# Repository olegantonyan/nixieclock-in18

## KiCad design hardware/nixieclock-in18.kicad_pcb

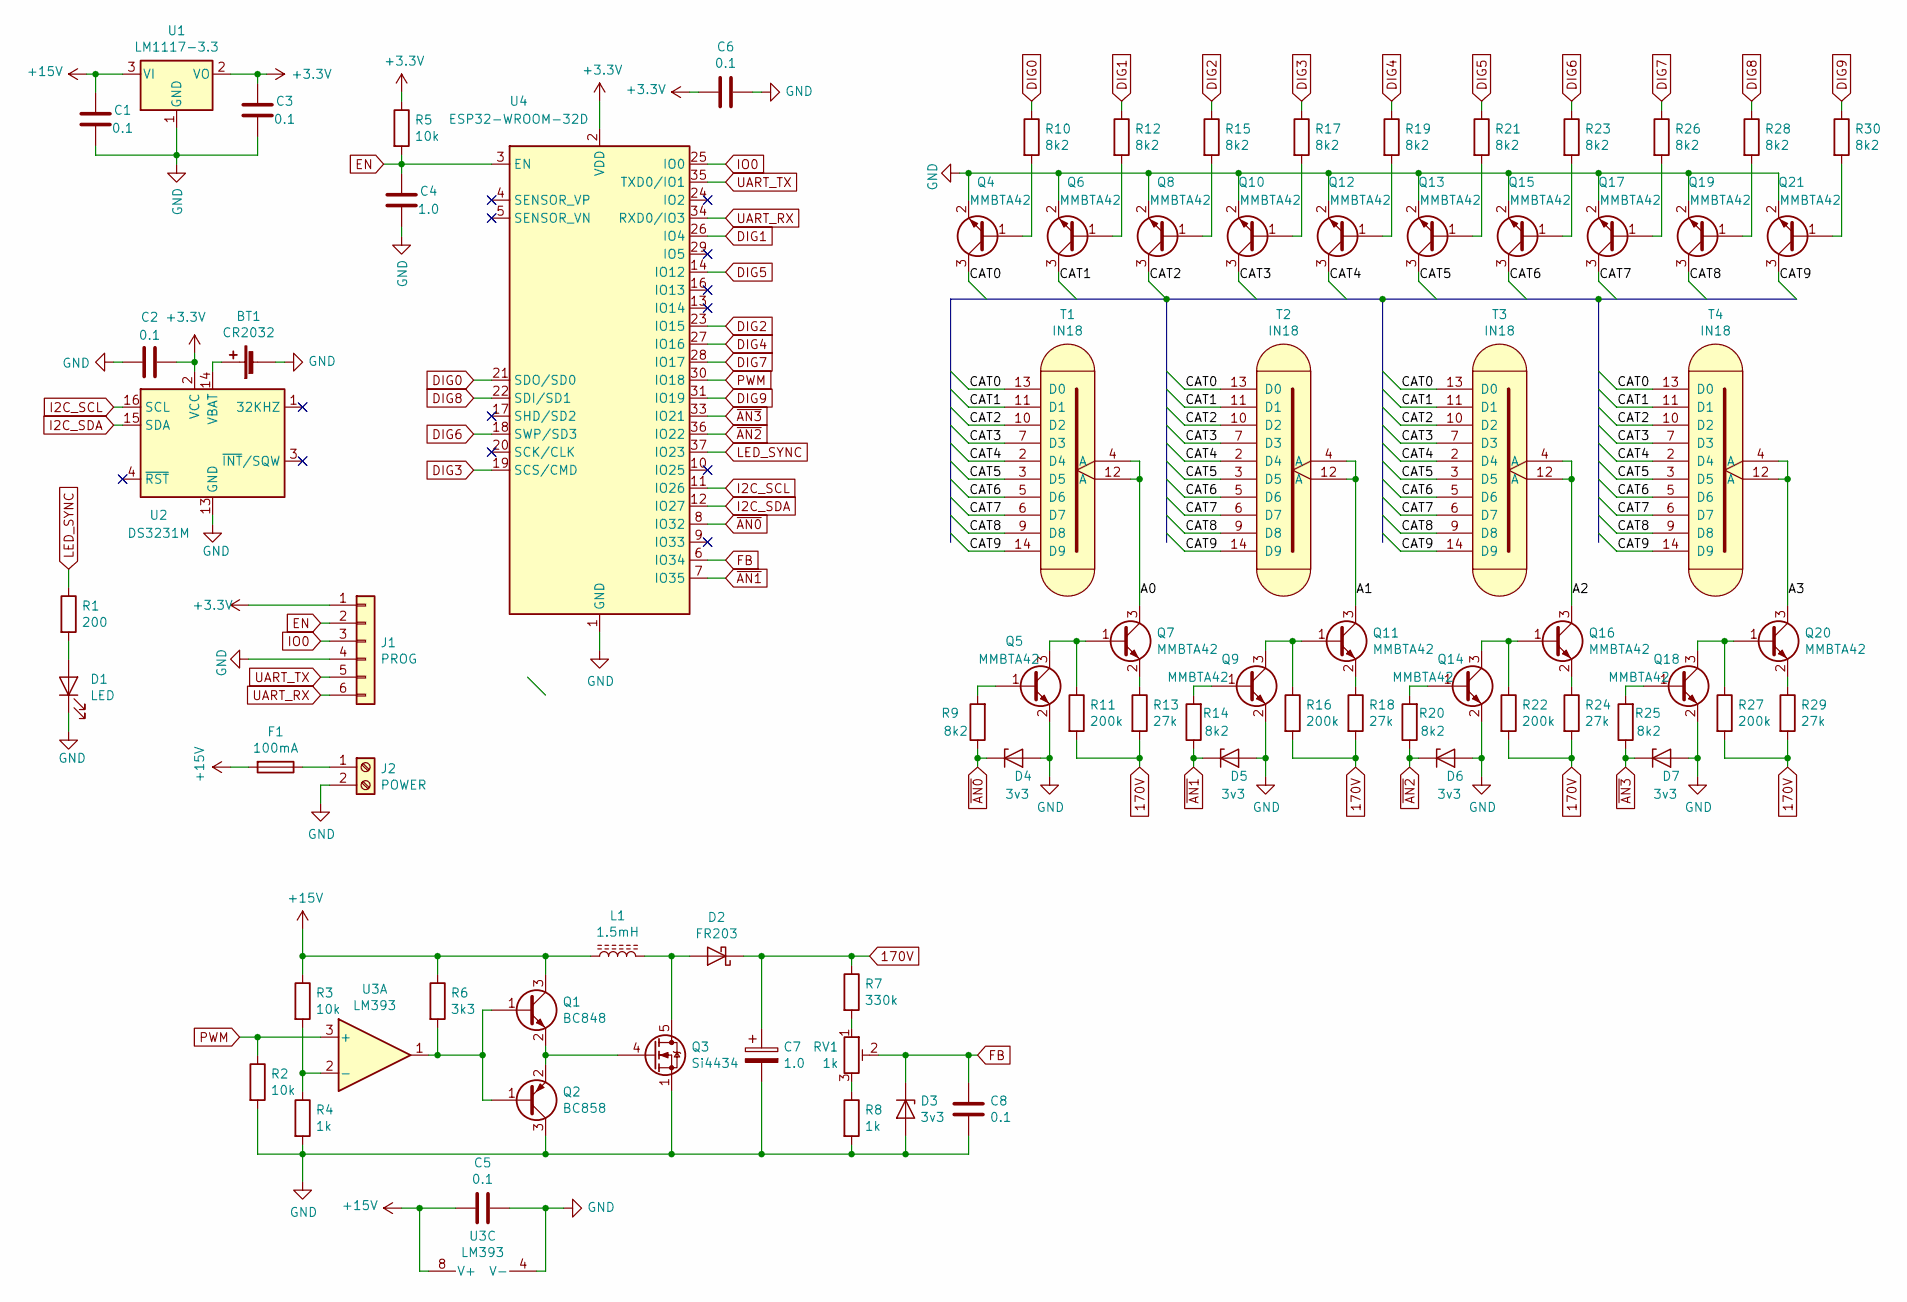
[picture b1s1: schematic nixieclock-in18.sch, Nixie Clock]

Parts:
BT1: CR2032; Keystone_103_1x20mm-CoinCell
C1, C2, C3, C5, C6, C8: 0.1; C_0805_HandSoldering
C4: 1.0; C_0805_HandSoldering
C7: 1.0; CP_Radial_D10.0mm_P5.00mm
D1: LED; LED_D3.0mm_FlatTop
D2: FR203; D_A-405_P10.16mm_Horizontal
D3, D4, D5, D6, D7: 3v3; D_DO-41_SOD81_P7.62mm_Horizontal
F1: 100mA; R_0805_HandSoldering
J1: PROG; Pin_Header_Straight_1x06_Pitch2.54mm
J2: POWER; TerminalBlock_bornier-2_P5.08mm
L1: 1.5mH; L_Radial_D12.0mm_P6.00mm_MuRATA_1900R
Q1: BC848; SOT-23_Handsoldering
Q2: BC858; SOT-23_Handsoldering
Q3: Si4434; PowerPAK_SO-8_Single
Q4, Q5, Q6, Q7, Q8, Q9, Q10, Q11, Q12, Q13, Q14, Q15, Q16, Q17, Q18, Q19, Q20, Q21: MMBTA42; SOT-23_Handsoldering
R1: 200; R_0805_HandSoldering
R2, R3, R5: 10k; R_0805_HandSoldering
R4: 1k; R_0805_HandSoldering
R6: 3k3; R_0805_HandSoldering
R7: 330k; R_Axial_DIN0207_L6.3mm_D2.5mm_P10.16mm_Horizontal
R8: 1k; R_Axial_DIN0207_L6.3mm_D2.5mm_P10.16mm_Horizontal
R9, R10, R12, R14, R15, R17, R19, R20, R21, R23, R25, R26, R28, R30: 8k2; R_0805_HandSoldering
R11, R16, R22, R27: 200k; R_0805_HandSoldering
R13, R18, R24, R29: 27k; R_0805_HandSoldering
RV1: 1k; Potentiometer_Trimmer_ACP_CA6v_Horizontal
T1, T2, T3, T4: IN18
U1: LM1117-3.3; SOT-223
U2: DS3231M; SOIC-16W_7.5x10.3mm_Pitch1.27mm
U3: LM393; SOIC-8_3.9x4.9mm_Pitch1.27mm
U4: ESP32-WROOM-32D; ESP32-WROOM

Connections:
170V: C7.1, D2.1 (K), R7.1, R11.2, R13.2, R16.2, R18.2, R22.2, R24.2, R27.2, R29.2
+3V3: C2.2, C3.2, C6.2, J1.1, R5.1, U1.2 (VO), U2.2 (VCC), U4.2 (VDD)
+15V: C1.2, C5.2, F1.2, L1.1, Q1.3 (C), R3.1, R6.1, U1.3 (VI), U3.8 (V+)
/A0: Q7.3 (C), T1.4 (A), T1.12 (A)
/A1: Q11.3 (C), T2.4 (A), T2.12 (A)
/A2: Q16.3 (C), T3.4 (A), T3.12 (A)
/A3: Q20.3 (C), T4.4 (A), T4.12 (A)
/CAT0: Q4.3 (C), T1.13 (D0), T2.13 (D0), T3.13 (D0), T4.13 (D0)
/CAT1: Q6.3 (C), T1.11 (D1), T2.11 (D1), T3.11 (D1), T4.11 (D1)
/CAT2: Q8.3 (C), T1.10 (D2), T2.10 (D2), T3.10 (D2), T4.10 (D2)
/CAT3: Q10.3 (C), T1.7 (D3), T2.7 (D3), T3.7 (D3), T4.7 (D3)
/CAT4: Q12.3 (C), T1.2 (D4), T2.2 (D4), T3.2 (D4), T4.2 (D4)
/CAT5: Q13.3 (C), T1.3 (D5), T2.3 (D5), T3.3 (D5), T4.3 (D5)
/CAT6: Q15.3 (C), T1.5 (D6), T2.5 (D6), T3.5 (D6), T4.5 (D6)
/CAT7: Q17.3 (C), T1.6 (D7), T2.6 (D7), T3.6 (D7), T4.6 (D7)
/CAT8: Q19.3 (C), T1.9 (D8), T2.9 (D8), T3.9 (D8), T4.9 (D8)
/CAT9: Q21.3 (C), T1.14 (D9), T2.14 (D9), T3.14 (D9), T4.14 (D9)
DIG0: R10.1, U4.21 (SDO/SD0)
DIG1: R12.1, U4.26 (IO4)
DIG2: R15.1, U4.23 (IO15)
DIG3: R17.1, U4.19 (SCS/CMD)
DIG4: R19.1, U4.27 (IO16)
DIG5: R21.1, U4.14 (IO12)
DIG6: R23.1, U4.18 (SWP/SD3)
DIG7: R26.1, U4.28 (IO17)
DIG8: R28.1, U4.22 (SDI/SD1)
DIG9: R30.1, U4.31 (IO19)
EN: C4.2, J1.2, R5.2, U4.3 (EN)
FB: C8.1, D3.1 (K), RV1.2, U4.6 (IO34)
GND: BT1.2 (-), C1.1, C2.1, C3.1, C4.1, C5.1, C6.1, C7.2, C8.2, D1.1 (K), D3.2 (A), D4.2 (A), D5.2 (A), D6.2 (A), D7.2 (A), J1.4, J2.2, Q2.3 (C), Q3.1 (S), Q3.2 (S), Q3.3 (S), Q4.2 (E), Q5.2 (E), Q6.2 (E), Q8.2 (E), Q9.2 (E), Q10.2 (E), Q12.2 (E), Q13.2 (E), Q14.2 (E), Q15.2 (E), Q17.2 (E), Q18.2 (E), Q19.2 (E), Q21.2 (E), R2.2, R4.2, R8.2, U1.1 (GND), U2.5 (GND), U2.6 (GND), U2.7 (GND), U2.8 (GND), U2.9 (GND), U2.10 (GND), U2.11 (GND), U2.12 (GND), U2.13 (GND), U3.4 (V-), U4.1 (GND), U4.15 (GND), U4.38 (GND)
I2C_SCL: U2.16 (SCL), U4.11 (IO26)
I2C_SDA: U2.15 (SDA), U4.12 (IO27)
IO0: J1.3, U4.25 (IO0)
LED_SYNC: R1.1, U4.37 (IO23)
unnamed: BT1.1 (+), U2.14 (VBAT)
unnamed: D1.2 (A), R1.2
unnamed: D2.2 (A), L1.2, Q3.5 (D)
unnamed: F1.1, J2.1
unnamed: Q1.1 (B), Q2.1 (B), R6.2, U3.1
unnamed: Q1.2 (E), Q2.2 (E), Q3.4 (G)
unnamed: Q4.1 (B), R10.2
unnamed: Q5.1 (B), R9.2
unnamed: Q5.3 (C), Q7.1 (B), R11.1
unnamed: Q6.1 (B), R12.2
unnamed: Q7.2 (E), R13.1
unnamed: Q8.1 (B), R15.2
unnamed: Q9.1 (B), R14.2
unnamed: Q10.1 (B), R17.2
unnamed: Q9.3 (C), Q11.1 (B), R16.1
unnamed: Q11.2 (E), R18.1
unnamed: Q12.1 (B), R19.2
unnamed: Q13.1 (B), R21.2
unnamed: Q14.1 (B), R20.2
unnamed: Q14.3 (C), Q16.1 (B), R22.1
unnamed: Q15.1 (B), R23.2
unnamed: Q16.2 (E), R24.1
unnamed: Q17.1 (B), R26.2
unnamed: Q18.1 (B), R25.2
unnamed: Q18.3 (C), Q20.1 (B), R27.1
unnamed: Q19.1 (B), R28.2
unnamed: Q20.2 (E), R29.1
unnamed: Q21.1 (B), R30.2
unnamed: R3.2, R4.1, U3.2 (-)
unnamed: R7.2, RV1.1
unnamed: R8.1, RV1.3
PWM: R2.1, U3.3 (+), U4.30 (IO18)
UART_RX: J1.6, U4.34 (RXD0/IO3)
UART_TX: J1.5, U4.35 (TXD0/IO1)
~AN0: D4.1 (K), R9.1, U4.8 (IO32)
~AN1: D5.1 (K), R14.1, U4.7 (IO35)
~AN2: D6.1 (K), R20.1, U4.36 (IO22)
~AN3: D7.1 (K), R25.1, U4.33 (IO21)

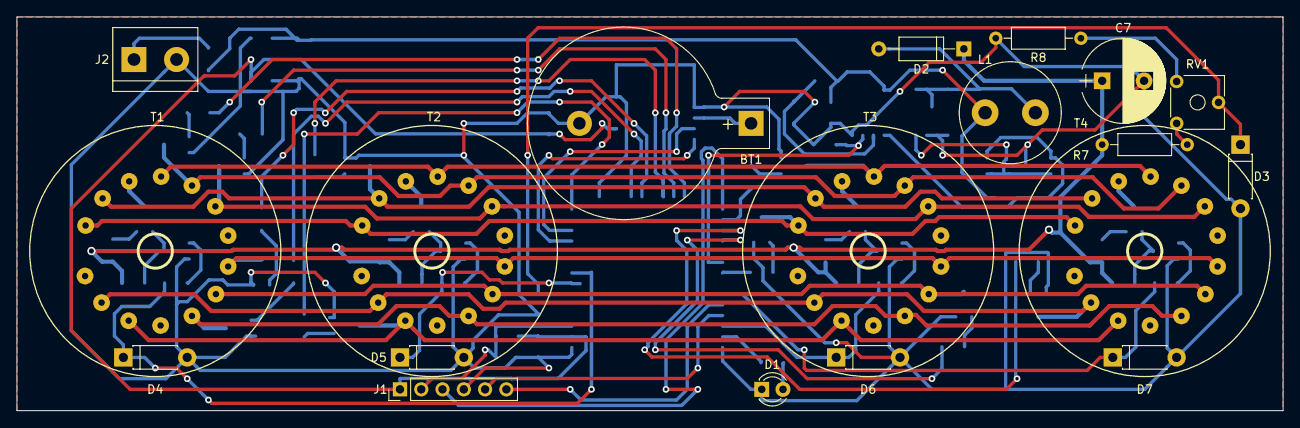
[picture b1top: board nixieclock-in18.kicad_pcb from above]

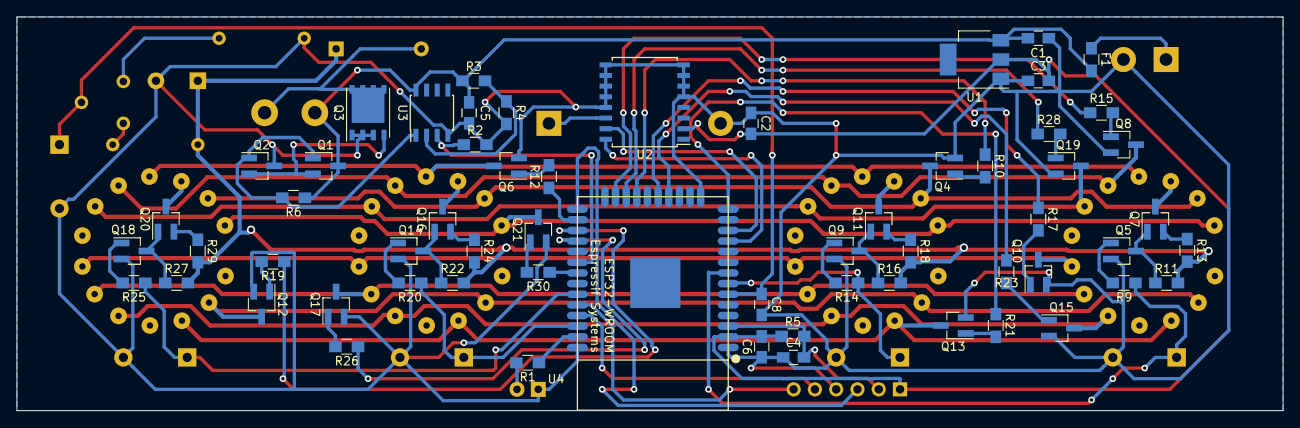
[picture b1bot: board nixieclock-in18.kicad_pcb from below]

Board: 2 copper layers, 151.1 x 47.0 mm, 80 parts (61 on the bottom side), 72 nets.

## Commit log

2019-08-26 initial
2019-08-26 initial 2
2019-08-26 working pwm
2019-08-29 pwm+adc works
2019-08-29 moar schematic
2019-08-31 pcb begins
2019-09-01 fix mmbta42 pinout
2019-09-03 finished pcb
2019-09-03 add fuse
2019-09-03 gerbers
2019-09-25 change DIG5 pin (programmin flash issue)
